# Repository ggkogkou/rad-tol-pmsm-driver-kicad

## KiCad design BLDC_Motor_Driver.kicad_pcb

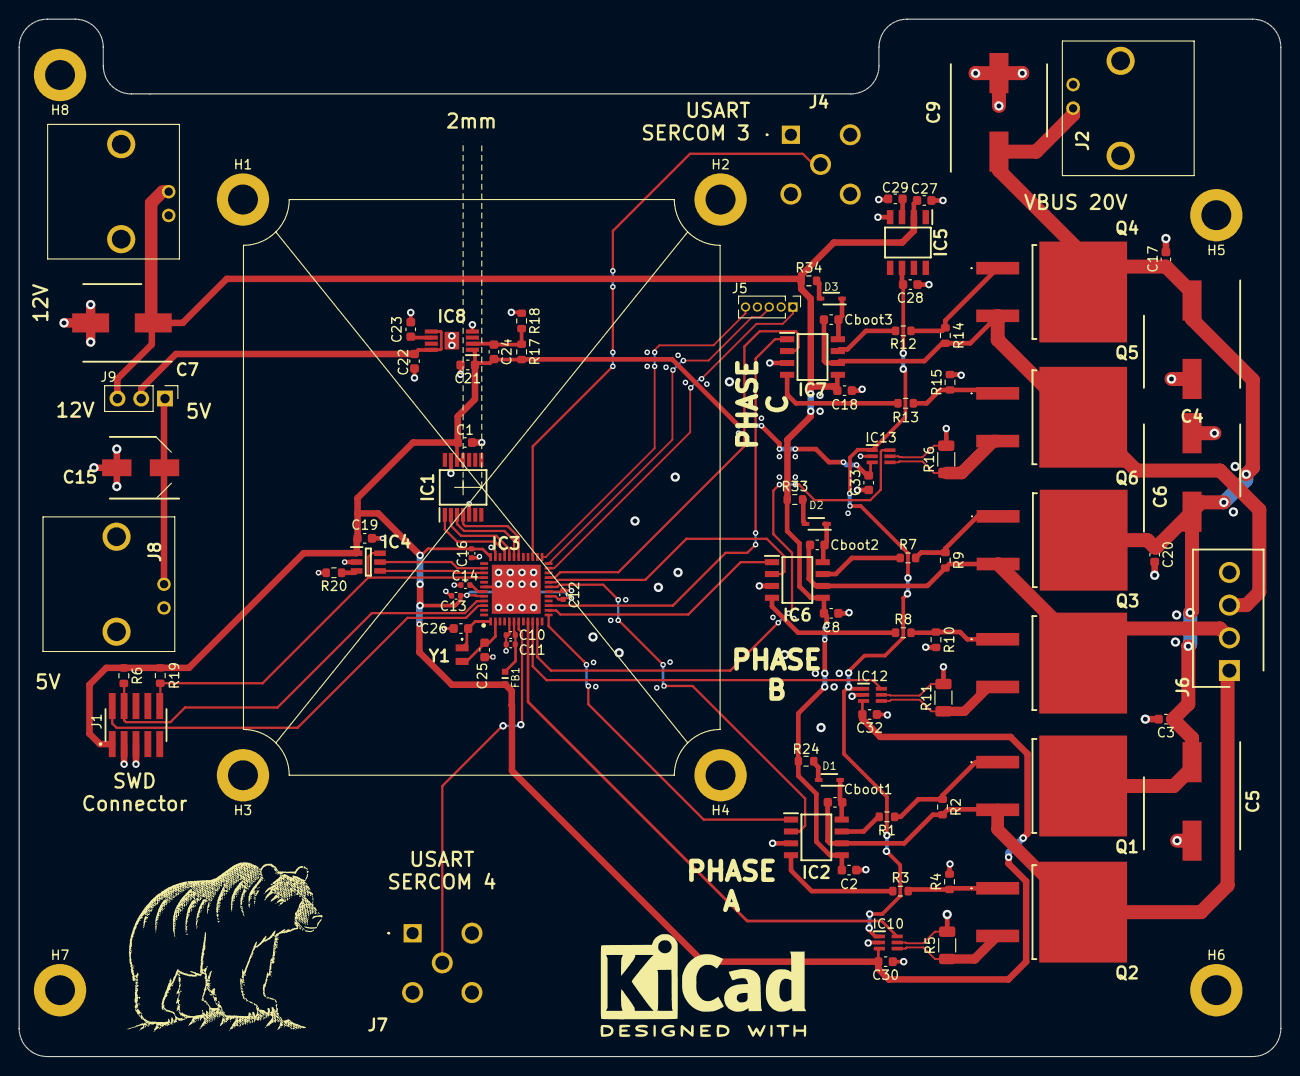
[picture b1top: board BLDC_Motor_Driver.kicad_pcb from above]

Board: 2 copper layers, 135.0 x 111.0 mm, 100 parts (0 on the bottom side), 65 nets.

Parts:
C1, C2, C8, C18, C19: 0.1uF; C_0603_1608Metric
C3, C17, C20: C; C_0603_1608Metric
C4, C5, C6, C9: 220uF; CAPAE1030X1050N
C7: 100uF; CAPAE830X1050N
C10, C12, C13, C16: 0.1u; C_0402_1005Metric
C11: 10u; C_0402_1005Metric
C14: 1u; C_0402_1005Metric
C15: 47uF; CAPAE660X770N
C21, C22: 10uF; C_0603_1608Metric
C23, C24, C29: 10nF; C_0603_1608Metric
C25, C26: 22pF; C_0603_1608Metric
C27, C28, C30, C32, C33: 0.1u; C_0603_1608Metric
Cboot1, Cboot2, Cboot3: 100nF; C_0603_1608Metric
D1, D2, D3: 1N4148WS
FB1: FerriteBead; BLM18SP221SN1B
H1, H2, H3, H4, H5, H6, H7, H8: MountingHole_Pad; MountingHole_3.2mm_M3_DIN965_Pad
IC1: AS5047P-ATSM; AS5047P
IC2, IC6, IC7: L6498D; L6498D-SO8
IC3: ATSAMD21G18A-MFT; SAM21G18A-QFN48
IC4: TPL5010DDCT
IC5: ISL21090BFB812Z-TK; ISL21090
IC8: TPS7A4901DGNT; TPS7A_LDO
IC10, IC12, IC13: INA214AIDCKT
J1: FTSH-105-01-L-DV-K; SAMTEC_FTSH-105-01-L-DV-K
J2, J3, J8: 031-5431-10RFX; 031543110RFX
J4, J7: 112405-12; 11240512
J5: Conn_01x05_Pin; PinHeader_1x05_P1.27mm_Vertical
J6: Conn_01x04_Socket; SHDR4W91P0X350_1X4_1400X730X875P
J9: Conn_01x03_Pin; PinHeader_1x03_P2.54mm_Vertical
NT1, NT2, NT3: NetTie_2; NetTie-2_SMD_Pad0.5mm
Q1, Q2, Q3, Q4, Q5, Q6: IPB320N20N3GATMA1
R1, R3, R7, R8, R12, R13: 50; R_0603_1608Metric
R2, R4, R6, R9, R10, R14, R15, R19: 10kΩ; R_0603_1608Metric
R5, R11, R16: 10mΩ; R_1206_3216Metric
R17, R18: 1kΩ; R_0603_1608Metric
R20: 20kΩ,1%; R_0603_1608Metric
R24, R33, R34: 2.2Ω; R_0603_1608Metric
Y1: ABS06-32.768KHZ-1-T; ABS06

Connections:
+3V3: C1.1, C12.1, C13.1, C16.1, C19.1, C21.1, C24.1, C30.2, C32.2, C33.2, FB1.1, IC1.11 (VDD), IC1.12 (VDD3V), IC3.17 (VDDIO_1), IC3.36 (VDDIO_2), IC3.44 (VDDIN), IC4.1 (VDD), IC8.1 (OUT), IC10.3 (V+), IC12.3 (V+), IC13.3 (V+), J1.01, R6.1, R17.1, R19.1
+5V: C15.1, J8.2, J9.1
+12V: C2.1, C7.1, C8.1, C18.1, C27.2, IC2.5 (VCC), IC5.2 (VIN), IC6.5 (VCC), IC7.5 (VCC), J3.2, J9.3, R24.2, R33.2, R34.2
/Current Sensing Difference Amplifier/CSA_PH_A_IN+: IC10.4 (IN+), Q2.3 (S), R5.1
/Current Sensing Difference Amplifier/CSA_PH_A_IN-: IC10.5 (IN-), NT2.2, R5.2
/Current Sensing Difference Amplifier/CSA_PH_A_VOUT: IC3.9 (PA04), IC10.6 (OUT)
/Current Sensing Difference Amplifier/CSA_PH_B_IN+: IC12.4 (IN+), Q4.3 (S), R11.1
/Current Sensing Difference Amplifier/CSA_PH_B_IN-: IC12.5 (IN-), NT1.2, R11.2
/Current Sensing Difference Amplifier/CSA_PH_B_VOUT: IC3.10 (PA05), IC12.6 (OUT)
/Current Sensing Difference Amplifier/CSA_PH_C_IN+: IC13.4 (IN+), Q6.3 (S), R16.1
/Current Sensing Difference Amplifier/CSA_PH_C_IN-: IC13.5 (IN-), NT3.2, R16.2
/Current Sensing Difference Amplifier/CSA_PH_C_VOUT: IC3.11 (PA06), IC13.6 (OUT)
/Current Sensing Difference Amplifier/VREF: C28.2, IC5.6 (VOUT), IC10.1 (REF), IC12.1 (REF), IC13.1 (REF)
/LDO_INPUT: C22.1, IC8.5 (EN), IC8.8 (IN), J9.2
/Microcontroller/BENCHMARK_IO_1: IC3.23 (PA14), J5.1
/Microcontroller/BENCHMARK_IO_2: IC3.24 (PA15), J5.3
/Microcontroller/BENCHMARK_IO_3: IC3.25 (PA16), J5.5
/Microcontroller/EXT_WDT_DONE: IC3.39 (PA27), IC4.4 (DONE)
/Microcontroller/EXT_WDT_WAKE: IC3.38 (PB23), IC4.5 (WAKE)
/Microcontroller/RESET: IC3.40 (~RESET), IC4.6 (RSTN), J1.10, R19.2
/Microcontroller/SERCOM3_PAD2: IC3.27 (PA18), J4.5
/Microcontroller/SERCOM4_PAD0: IC3.7 (PB08), J7.5
/Microcontroller/SERCOM5_PAD0: IC1.3 (MISO), IC3.31 (PA22)
/Microcontroller/SERCOM5_PAD1: IC1.2 (CLK), IC3.32 (PA23)
/Microcontroller/SERCOM5_PAD2: IC1.1 (CSN), IC3.33 (PA24)
/Microcontroller/SERCOM5_PAD3: IC1.4 (MOSI), IC3.30 (PA21)
/Microcontroller/SWCLK: IC3.45 (PA30), J1.04, R6.2
/Microcontroller/SWDIO: IC3.46 (PA31), J1.02
/Microcontroller/TCC0_WO0: IC2.1 (HIN), IC3.13 (PA08)
/Microcontroller/TCC0_WO1: IC3.14 (PA09), IC6.1 (HIN)
/Microcontroller/TCC0_WO2: IC3.15 (PA10), IC7.1 (HIN)
/Microcontroller/TCC0_WO4: IC2.2 (LIN), IC3.19 (PB10)
/Microcontroller/TCC0_WO5: IC3.20 (PB11), IC6.2 (LIN)
/Microcontroller/TCC0_WO6: IC3.21 (PA12), IC7.2 (LIN)
/Microcontroller/VDDANA: C10.1, C11.1, FB1.2, IC3.6 (VDDANA)
/Microcontroller/VDDCORE: C14.1, IC3.43 (VDDCORE)
/Microcontroller/XIN32: C26.1, IC3.1 (PA00), Y1.1
/Microcontroller/XOUT32: C25.1, IC3.2 (PA01), Y1.2
/Power Stage - Inverter & Gate Drivers/OUT_PHASE_A: Cboot1.2, IC2.6 (OUT), J6.1, Q1.3 (S), Q2.2 (D), R2.2
/Power Stage - Inverter & Gate Drivers/OUT_PHASE_B: Cboot2.2, IC6.6 (OUT), J6.2, Q3.3 (S), Q4.2 (D), R9.2
/Power Stage - Inverter & Gate Drivers/OUT_PHASE_C: Cboot3.2, IC7.6 (OUT), J6.3, Q5.3 (S), Q6.2 (D), R14.2
GND: C1.2, C2.2, C3.2, C4.2, C5.2, C6.2, C7.2, C8.2, C9.2, C10.2, C11.2, C12.2, C13.2, C14.2, C15.2, C16.2, C17.2, C18.2, C19.2, C20.2, C21.2, C22.2, C23.2, C25.2, C26.2, C27.1, C28.1, C29.1, C30.1, C32.1, C33.1, H4.1, H8.1, IC1.5 (TEST), IC1.13 (GND), IC2.3 (GND), IC3.5 (GNDANA), IC3.18 (GND_1), IC3.35 (GND_2), IC3.42 (GND_3), IC3.49 (GND_4), IC4.2 (GND), IC5.4 (GND), IC6.3 (GND), IC7.3 (GND), IC8.4 (GND), IC8.9 (POWERPAD), IC10.2 (GND), IC12.2 (GND), IC13.2 (GND), J1.03, J1.05, J2.1, J3.1, J4.4, J5.2, J5.4, J6.4, J7.4, J8.1, NT1.1, NT2.1, NT3.1, R4.2, R10.2, R15.2, R18.2, R20.2
unnamed: D1.2 (A), R24.1
unnamed: Cboot1.1, D1.1 (K), IC2.8 (BOOT)
unnamed: D2.2 (A), R33.1
unnamed: Cboot2.1, D2.1 (K), IC6.8 (BOOT)
unnamed: D3.2 (A), R34.1
unnamed: Cboot3.1, D3.1 (K), IC7.8 (BOOT)
unnamed: IC2.7 (HVG), R1.1
unnamed: IC2.4 (LVG), R3.1
unnamed: IC4.3 (DELAY/M_RST), R20.1
unnamed: C29.2, IC5.3 (COMP)
unnamed: IC6.7 (HVG), R7.1
unnamed: IC6.4 (LVG), R8.1
unnamed: IC7.7 (HVG), R12.1
unnamed: IC7.4 (LVG), R13.1
unnamed: C24.2, IC8.2 (FB), R17.2, R18.1
unnamed: C23.1, IC8.6 (NR/SS)
unnamed: Q1.1 (G), R1.2, R2.1
unnamed: Q2.1 (G), R3.2, R4.1
unnamed: Q3.1 (G), R7.2, R9.1
unnamed: Q4.1 (G), R8.2, R10.1
unnamed: Q5.1 (G), R12.2, R14.1
unnamed: Q6.1 (G), R13.2, R15.1
VBUS: C3.1, C4.1, C5.1, C6.1, C9.1, C17.1, C20.1, J2.2, Q1.2 (D), Q3.2 (D), Q5.2 (D)

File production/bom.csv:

Designator,Footprint,Quantity,Value,LCSC Part #
"C1, C18, C19, C2, C8",0603,5,0.1uF,
"C10, C12, C13, C16",0402,4,0.1u,
C11,0402,1,10u,
C14,0402,1,1u,
C15,CAPAE660X770N,1,47uF,
"C17, C20, C3",0603,3,C,
"C21, C22",0603,2,10uF,
"C23, C24, C29",0603,3,10nF,
"C25, C26",0603,2,22pF,
"C27, C28, C30, C32, C33",0603,5,0.1u,
"C4, C5, C6, C9",CAPAE1030X1050N,4,220uF,
C7,CAPAE830X1050N,1,100uF,
"CBOOT1, CBOOT2, CBOOT3",0603,3,100nF,
"D1, D2, D3",1N4148WS,3,1N4148WS,
FB1,BLM18SP221SN1B,1,FerriteBead,
IC1,AS5047P,1,AS5047P-ATSM,
"IC10, IC12, IC13",INA214AIDCKT,3,INA214AIDCKT,
"IC2, IC6, IC7",L6498D-SO8,3,L6498D,
IC3,SAM21G18A-QFN48,1,ATSAMD21G18A-MFT,
IC4,TPL5010DDCT,1,TPL5010DDCT,
IC5,ISL21090,1,ISL21090BFB812Z-TK,
IC8,TPS7A_LDO,1,TPS7A4901DGNT,
J1,SAMTEC_FTSH-105-01-L-DV-K,1,FTSH-105-01-L-DV-K,
"J2, J3, J8",031543110RFX,3,031-5431-10RFX,
"J4, J7",11240512,2,112405-12,
J5,PinHeader_1x05_P1.27mm_Vertical,1,Conn_01x05_Pin,
J6,SHDR4W91P0X350_1X4_1400X730X875P,1,Conn_01x04_Socket,
J9,PinHeader_1x03_P2.54mm_Vertical,1,Conn_01x03_Pin,
"Q1, Q2, Q3, Q4, Q5, Q6",IPB320N20N3GATMA1,6,IPB320N20N3GATMA1,
"R1, R12, R13, R3, R7, R8",0603,6,50,
"R10, R14, R15, R19, R2, R4, R6, R9",0603,8,10kΩ,
"R11, R16, R5",1206,3,10mΩ,
"R17, R18",0603,2,1kΩ,
R20,0603,1,"20kΩ,1%",
"R24, R33, R34",0603,3,2.2Ω,
Y1,ABS06,1,ABS06-32.768KHZ-1-T,

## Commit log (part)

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2026-03-25 Initial layout
2026-03-26 Almost all routing done
2026-03-26 Add gitgnore file
2026-03-26 Clear Git cache
2026-03-27 More routing
2026-03-27 Add capacitors
2026-03-28 Add 5V rail available for LDO input
2026-03-28 Add more vias
2026-03-28 Keep=away zone
2026-03-28 Add step file
2026-04-12 Finalize design
